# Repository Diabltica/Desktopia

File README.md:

# Desktopia

Desktopia is an open-source project for easy height control of your IKEA Skarsta/Trotten sit-stand desk, providing a
comfortable and customizable workspace experience.

A DC motor replaces the crank handle. Two boards control it: the **motherboard** under the desk top, and the **HMI board**
on the front edge with a round screen and five buttons. A time-of-flight sensor measures the desk height, so the desk can
go back to three saved heights at the press of a button.

## How it works

```mermaid
flowchart LR
    PSU[24 V power supply] -->|J1| MB
    subgraph MB[Motherboard - RP2040]
        direction TB
        SHUNT[2 mΩ shunt + INA226]
        SW[P-MOSFET supply switch]
        TOF[VL53L1CB height sensor]
    end
    MB -->|J5: switched 24 V| DRV[Cytron MD10C motor driver]
    MB -->|J6: DIR + PWM + GND| DRV
    DRV --> MOTOR[Motor] --> GEAR[Gearbox] --> DESK[Desk]
    MB <-->|RJ11 cord: 5 V + RS-485| HMI[HMI board - RP2040<br/>round screen + 5 buttons]
```

- The **motherboard** makes every decision. It reads the height (VL53L1CB), runs the state machine, drives the motor
  driver (direction + PWM, with ramps) and stores the presets in its flash. It also switches the driver's 24 V supply:
  on for a move, off after 5 minutes without one, and off at once if the motor current goes over the limit (INA226).
- The **HMI board** only displays what the motherboard sends and reports the button levels. It is powered by the
  motherboard through the RJ11 cord, which also carries the RS-485 link (250 kbaud, polled every 10 ms).
- If the cord, the sensor or the firmware fails, or the motor draws too much current, the motor stops: see the protections in
  [firmware/README.md](firmware/README.md#built-in-protections).

## Usage

| Action | Result |
|---|---|
| **Up / Down** held | the desk moves as long as the button is held |
| **Preset 1-3**, short press | the desk goes to the saved height |
| **Preset 1-3**, long press (2 s) | the current height is saved |
| any button during an automatic move | stop |

## Repository layout

| Folder | Content | Documentation |
|---|---|---|
| [hardware/desktopia/](hardware/desktopia/) | motherboard KiCad project (schematic, PCB) | [README](hardware/desktopia/README.md) |
| [hardware/desktopia_HMI/](hardware/desktopia_HMI/) | HMI board KiCad project (schematic, PCB) | [README](hardware/desktopia_HMI/README.md) |
| [hardware/kicad_library/](hardware/kicad_library/) | symbols and footprints shared by both KiCad projects (`JLCImport`, ...) | |
| [hardware/render.sh](hardware/render.sh) | renders the schematic / PCB / 3D images of the board READMEs; run by the [*Hardware images*](.github/workflows/hardware-images.yml) workflow on every push | |
| [firmware/desktopia/](firmware/desktopia/) | motherboard firmware (RP2040, PlatformIO) | [README](firmware/desktopia/README.md) |
| [firmware/desktopia_HMI/](firmware/desktopia_HMI/) | HMI board firmware (RP2040, PlatformIO) | [README](firmware/desktopia_HMI/README.md) |
| [firmware/shared/hmi_link/](firmware/shared/hmi_link/) | link protocol and screen model, compiled into both firmwares | [hmi_protocol.h](firmware/shared/hmi_link/hmi_protocol.h) |
| [firmware/sim/](firmware/sim/) | PC simulation of both boards from their real sources (Linux / WSL) | [README](firmware/README.md#simulation-bench-optional) |
| [mechanical/](mechanical/) | 3D-printed motor supports with silent blocks and jaw coupling (CadQuery scripts, STL / STEP, assembly report) | [README](mechanical/README.md) |
| [documentation/](documentation/) | VL53L1X datasheet | |

## Getting started

Tools: [KiCad 10](https://www.kicad.org/) for the boards, [PlatformIO](https://platformio.org/) for the firmwares.

1. **Boards**: open each KiCad project, update the PCB from the schematic and order it. Every assembled part has its
   JLCPCB / LCSC number in the `LCSC` field. Read the board READMEs first: both PCBs still have to be updated after
   the latest schematic changes.
2. **HMI firmware**: `cd firmware/desktopia_HMI && pio run -t upload` with the board in USB boot mode.
3. **Motherboard firmware**: `cd firmware/desktopia && pio run -t upload` (the board must be powered from its 24 V input).
4. **First power-up**: follow [the checklist](firmware/README.md#first-power-up-do-it-in-this-order), with the motor
   decoupled from the desk at first.

The firmware of both boards can be tested on a PC without any hardware (`firmware/sim/`, Linux / WSL).

## Status

- Firmwares: build with no warnings; tested in the PC simulation only.
- Schematics: ERC checked, netlists checked by script.
- PCBs: **not yet updated** to the latest schematics (RJ11 link, RP2040 HMI board, power input, current sensor, motor supply switch).
- Nothing has been tested on real boards yet.

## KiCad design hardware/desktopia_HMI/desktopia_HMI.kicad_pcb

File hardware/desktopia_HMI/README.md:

# Desktopia – HMI board

KiCad 10 project: `desktopia_HMI.kicad_sch`, `desktopia_HMI.kicad_pcb`. Firmware: [../../firmware/desktopia_HMI/](../../firmware/desktopia_HMI/README.md).

The HMI board sits on the front edge of the desk. It carries the round screen and the five buttons. Its own RP2040
draws the screen, debounces the buttons and answers the motherboard over RS-485. A single RJ11 cord brings both the
power and the link.

## Views

Interactive viewer (KiCanvas, opens the files of the `main` branch in the browser):
[schematic](https://kicanvas.org/?github=https://github.com/Diabltica/Desktopia/blob/main/hardware/desktopia_HMI/desktopia_HMI.kicad_sch) · [PCB](https://kicanvas.org/?github=https://github.com/Diabltica/Desktopia/blob/main/hardware/desktopia_HMI/desktopia_HMI.kicad_pcb).

The images below are rendered by [`../render.sh`](../render.sh) and committed by the
[*Hardware images*](../../.github/workflows/hardware-images.yml) workflow on every push that touches `hardware/`.
Click an image to open it full size.
The screen module model (`RoundLCD.wrl`) shows the real UI, taken from a screenshot of the simulator: it is generated by
[`round_lcd_3d.py`](../kicad_library/pcb/tools/round_lcd_3d.py) (rerun it after `firmware/sim/run.sh` to show another screen).
The picture is turned the way the firmware draws it for the module's position on the board (see J2 below).
The cord soldered to J3 (`Cable_6P6C_SolderPads.wrl`: about 1 cm of cord, the six wires, the solder joints and the
cable tie) is generated by [`cable_6p6c_3d.py`](../kicad_library/pcb/tools/cable_6p6c_3d.py).

Reading the schematic: every connection is a wire, with no labels. The parts sit next to the RP2040 pins they use:
the flash, crystal, USB, RUN and SWD on its left; the RS-485 transceiver, the buttons and the screen connector on its
right. Wires that cross without a dot are not connected: GPIO0 (to DI) over GPIO1 / GPIO2, and the screen CS (GPIO17)
over SCK / MOSI / DC, because the connector pin order differs from the GPIO order.
Each block has its own background and title colour (power and USB, RP2040 and flash, RS-485 link, buttons, screen).
Wires take the colour of their net class, as on the motherboard, with a legend at the bottom left of the sheet:
orange +5V, purple +3V3, pink +1V1, grey GND, teal the buses (USB, RS-485 and its UART, QSPI, screen SPI), green the
rest. See *PCB rules*.

**Schematic**

**PCB**

| Front | Back (mirrored) |
|---|---|
|  |  |

**3D**

| Top | Bottom |
|---|---|
|  |  |

## Blocks

| Block | Parts | Notes |
|---|---|---|
| MCU | U3 RP2040, Y1 12 MHz (C8 / C10 33 pF, R6 1k), decoupling C4-C7, C9, C11-C19 | standard Raspberry Pi minimal design |
| Flash | U2 W25Q128JVSIQ (16 MB QSPI) | the firmware uses 2 MB |
| 3.3 V | U1 XC6206P332 LDO, C1 / C2 (input), C3 (output) | supplies the RP2040, flash and transceiver |
| Link | J3 solder pads for the 6P6C cord, U4 SP3485EN (3.3 V RS-485), R8 120 Ω (not assembled) | UART0: GP0 TX, GP1 RX, GP2 DE + /RE |
| USB | J1 USB-C (G-Switch GT-USB-7010ASV), D1 SS14, R1 / R3 5.1k on CC, R4 / R2 22 Ω (D+ / D-) | bench flashing only |
| Boot / debug | SW1 BOOT (QSPI_SS through R5 1k), R7 10k RUN pull-up, TP1-TP4 SWD | no reset button: replug, or ground TP2 (RUN) |
| Screen | J2 7-pin connector, TP5-TP9 | GC9A01 240×240 round LCD on SPI0 |
| Buttons | SW2-SW6 Kailh Choc hot-swap sockets (PG1350) | to GND, internal pull-ups |

## Connectors

| Ref | Function | Pin-out |
|---|---|---|
| J1 | USB-C | flashing (UF2 bootloader) |
| J2 | round LCD | 1 = RST (GP21), 2 = CS (GP17), 3 = DC (GP20), 4 = MOSI (GP19), 5 = SCK (GP18), 6 = GND, 7 = +5 V |
| J3 | flat 6P6C cord to the motherboard, soldered (see below) | 1 = +5 V, 2 = GND, 3 = A, 4 = B, 5 = GND, 6 = +5 V |

J2 is numbered from the other end than the module's pin labels: the module's VCC, GND, SCL, SDA, DC, CS, RST are
J2 pins 7 down to 1.

The module sits with its pin header towards the buttons (J2 at 90°), turned 180° from the first layout: the firmware
turns the picture to match (`DISPLAY_ROTATION` 3 in `firmware/desktopia_HMI/include/hmi_config.h`).

Buttons: SW6 Up = GP11, SW5 Down = GP12, SW4 / SW3 / SW2 Preset 1 / 2 / 3 = GP13 / GP14 / GP15. On the PCB (front
view) they sit from SW2 on the left to SW6 on the right.

## The cord (J3)

The board sits at 45° under the front edge of the desk, in a wedge-shaped housing. An RJ11 jack would stand 12 mm
off the board, and its cord would leave parallel or perpendicular to the board, so at 45° to the desk either way.
The cord is therefore **soldered**: J3 (`Desktopia:Cable_6P6C_SolderPads`) has six 1 mm holes at 2.54 mm and two
slots for a 2.5 mm cable tie. The cord lies against the **bottom** of the board, leaves over the board edge (the
dashed *board edge* line on the Fab layer) and folds flat against the underside of the desk. Only the motherboard end
has an RJ11 plug, so the cord is unplugged there.

1. Take a flat 6-conductor cord (6P6C, sometimes sold as "RJ12") with a plug on one end, or crimp one.
   4-conductor cords (6P4C) do not work.
2. Strip about 10 mm of the jacket, strip and tin 3 mm of each wire.
3. Push the wires through the holes from the bottom and solder them on the top, **in their flat order**, edge wire
   on pad 1. Either direction is fine: the pin-out is symmetric, and
   a mirrored order only swaps A and B, which the firmware detects. Never cross two wires. The Fab layer shows the
   usual colours (white, black, red, green, yellow, blue), for reference only.
4. Put a cable tie through the two slots around the jacket, just behind the stripped end, its head under the cord.

## Power

- The motherboard supplies 5 V through the cord, limited by its 500 mA PTC. The screen module takes the 5 V and
  regulates its own 3.3 V. Its logic is driven at 3.3 V by the RP2040.
- On the bench, USB-C powers the board through the Schottky D1, which keeps the cord's 5 V out of the USB host.
  Unplug the cord at the motherboard while flashing over USB: otherwise the USB also feeds the motherboard's 5 V rail through the cord.

## Flashing

First flash: hold **SW1 (BOOT)**, plug the USB-C cable, then release SW1. The board appears as a USB drive (RPI-RP2).
Then run `pio run -t upload`, or copy `firmware.uf2` onto the drive. Later updates work the same way, or through SWD
on TP4 (SWCLK) / TP3 (SWDIO) / TP1 (GND).

## Test points

| TP | Net | TP | Net |
|---|---|---|---|
| TP1 | GND | TP6 | LCD_MOSI |
| TP2 | RUN (ground it to reset) | TP7 | LCD_DC |
| TP3 | SWDIO | TP8 | LCD_CS |
| TP4 | SWCLK | TP9 | LCD_RST |
| TP5 | LCD_SCK | | |

## Assembly (JLCPCB)

Order: 5 PCBs (2 layers, 139.7 × 33.27 mm, 1.6 mm, HASL with lead, green), **Economic PCBA of 2 boards, bottom side**
(every SMD part sits on the bottom). The pricing rules are the motherboard's (see *Assembly* in its
[README](../desktopia/README.md)): €2.82 per Extended SMD part number, none for Basic parts, no 0201, and the OSP finish
greys out Economic PCBA. Every assembled part has its LCSC number in the `LCSC` and `jlcpcb PartNumber` fields. The
production files come from the Fabrication Toolkit plugin (`production/`: Gerber zip, `bom.csv`, `positions.csv`).

- One Extended part number is left, U3 (RP2040, C2040), with no Basic or Preferred substitute. Everything else is
  Basic, and the MCU block uses the motherboard's part numbers.
- **J1** (USB-C, Extended) is excluded from the BOM and the position files: you solder it, as J3 on the motherboard
  (see the hand-soldering notes in its README). Its loading fee costs more than the part.
- Y1 is the Basic X322512MSB4SI (C9002). It is specified for a 20 pF load, hence the 33 pF capacitors C8 / C10.
- J1 is the G-Switch GT-USB-7010ASV (C2988369, $0.09). It replaces the HRO TYPE-C-31-M-12 ($0.19); the pins are the
  same, the footprint is KiCad's `USB_C_Receptacle_G-Switch_GT-USB-7010ASV`.
- U2 stays the W25Q128JVSIQ (16 MB) because it is a Basic part. The 2 MB and 4 MB Winbond parts are Extended at JLCPCB
  and cost $1.0 to $1.4. With the loading fee, they only pay off from about 4 boards per order.
- **SW2-SW6**, the Kailh Choc hot-swap sockets (CPG135001S30, C5333465), are out of stock at JLCPCB *and* LCSC
  (November 28, 2026, under every part number): they are excluded from the BOM and the position files (symbol and
  footprint), and you solder them by hand. Buy 10 (2 boards × 5) from a keyboard parts shop, with the Choc switches.
- Not assembled: R8 (termination, only for cords over ~5 m) and the test points. J2 takes the screen module's
  cable.

The JLCONE quotes (November 28, 2026, in euros, 2 boards, VAT and shipping excluded):

| # | JLCPCB does not assemble | PCB (engineering + board) | Setup + stencil | Components | Extended fee | SMT | N₂ | JLCPCB |
|---|---|---|---|---|---|---|---|---|
| 1 | SW2-SW6 | 5.76 (3.65 + 2.10) | 8.95 | 7.34 | 5.65 (2) | 0.52 | 0.79 | **28.99** |
| 2 | 1 + J1 (**chosen**) | 5.76 | 8.95 | 7.03 | 2.82 (1) | 0.42 | 0.79 | **25.76** |

- The board is longer than 100 mm, so it misses the PCB special offer of the motherboard (€1.83 for 5) and pays the
  €3.65 engineering fee. It needs no X-ray inspection (the motherboard's €3.01 comes with its other leadless parts).
- Option 2 saves €2.84 once J1 is bought at LCSC (5 for both boards' USB-C: $0.42). Quote 2 was checked with the
  files of `production/`.
- Order both boards together: one parcel, one shipping fee. Each board stays its own PCBA order, so the RP2040 loading
  fee, the setup and the stencil are paid once per board. The LCSC parts of both boards are in the common cart
  [`../lcsc_cart.csv`](../lcsc_cart.csv) (upload it at LCSC's *BOM Tool*).
- 3D model of J1: the LCSC one (`kicad_library/pcb/JLCImport.3dshapes`), as on the motherboard. R8 has its model but
  is marked DNP, so the 3D view hides it.

## PCB rules

The method and the sources are the motherboard's (see *PCB rules* in its [README](../desktopia/README.md)): 2 layers,
FR-4 1.6 mm, 1 oz (35 µm) copper, made by JLCPCB, track currents from IPC-2221 at ΔT 10 °C. Every net here is at 5 V
or less, so one clearance fits all: 0.2 mm (IPC-2221B, uncoated pads up to 15 V: 0.13 mm; JLCPCB: 0.10 mm).

- *Board Setup → Constraints*: JLCPCB's absolute minimums, the same as on the motherboard (0.10 mm track and gap; via
  0.45 mm with a 0.2 mm hole; 0.2 mm hole to hole and hole to copper; 0.3 mm to the board edge; 0.1 mm solder mask web;
  1 mm / 0.15 mm silkscreen text).
- *Board Setup → Net Classes*: routing width, clearance and via of each class (below), also in the toolbar lists.
- [`desktopia_HMI.kicad_dru`](desktopia_HMI.kicad_dru) (*Board Setup → Custom Rules*): the DRC minimum width of each
  class, JLCPCB's hole and silkscreen rules, and the exceptions.

| Class | Nets | Track: routing / DRC min | Clearance | Via: pad / hole | A track carries |
|---|---|---|---|---|---|
| `Default` | crystal, SWD, RUN, buttons, BOOT, CC | 0.2 / 0.15 mm | 0.2 mm | 0.6 / 0.3 mm | 0.7 A |
| `Buses` | USB D+ / D-, RS-485 A / B and its UART, QSPI, screen SPI | 0.2 / 0.15 mm, pairs 0.2 mm with a 0.2 mm gap | 0.2 mm | 0.6 / 0.3 mm | 0.7 A |
| `Power_1V1` | +1V1 (RP2040 core) | 0.3 / 0.2 mm | 0.2 mm | 0.6 / 0.3 mm | 1.0 A |
| `Power_3V3` | +3V3 (XC6206, 0.2 A at most) | 0.3 / 0.2 mm | 0.2 mm | 0.6 / 0.3 mm | 1.0 A |
| `GND` | GND (pour on both layers) | 0.4 / 0.2 mm | 0.2 mm | 0.6 / 0.3 mm | 1.2 A |
| `Power_5V` | +5V, USB VBUS (0.5 A at most: the motherboard's PTC) | 0.4 / 0.2 mm | 0.2 mm | 0.6 / 0.3 mm | 1.2 A |

- A 0.6 / 0.3 mm via carries 0.7 A (ΔT 10 °C, 18 µm of hole plating): one is enough for every rail of this board.
- The RP2040 sets the 0.2 mm width: its 0.4 mm pitch pads are 0.2 mm wide and 0.2 mm apart, so a 0.2 mm track enters a
  pad 0.2 mm from the next one. The power tracks neck down to 0.2 mm (their DRC minimum) at its pins.
- Exceptions:
  - Pads of one footprint keep the maker's land pattern, at 0.15 mm at least: the USB-C GND pads sit 0.19 mm from the
    connector's locating holes.
  - Tracks inside the courtyard of U3 or J1 may pass 0.15 mm from other copper.
  - Holes of one footprint keep the 0.2 mm via spacing: the via ring of the M2 mounting holes is 0.35 mm apart.
- The other JLCPCB rules are the motherboard's: vias at least 0.6 / 0.3 mm, holes 0.2 to 6.3 mm, NPTH 0.5 mm at least,
  PTH annular ring 0.18 mm, pad holes of two footprints 0.45 mm apart, PTH hole to track 0.35 mm, silkscreen 0.15 mm
  from pads.

## PCB: what to do before ordering

The PCB is routed (no unconnected item), and the routing passes the net class rules. The DRC of November 11, 2026
still finds:

- **TP1-TP9 are missing from the PCB.** They are in the schematic, but it changed after the last PCB update. So the
  board has no SWD (TP1 / TP3 / TP4, see *Flashing*), RUN or screen test points. Run *Update PCB from Schematic*,
  then place and route them.
- **7 thermal reliefs with one spoke instead of two** (errors), all on B.Cu: pad 2 of C5, C16 and C18, and the four
  GND pads of J1. Add a track or a via to the pour, or give these pads a solid connection.
- **5 GND vias stacked at (84.2, 83.8) mm**: keep one.
- **The silkscreen labels of J3** (+5V, GND, A, B) are 0.6 mm high, under JLCPCB's 1 mm / 0.15 mm, and may not print.
  They come from the footprint ([`cable_6p6c_fp.py`](../kicad_library/pcb/tools/cable_6p6c_fp.py)).
- Warnings only:
  - silkscreen closer than 0.15 mm to pads (171): JLCPCB trims silkscreen off pads;
  - silkscreen over copper (65);
  - the H1 / H2 references and the J2 outline clipped by the board edge (4);
  - the NPTH holes of the PG1350 sockets drawn twice in their footprint (5).

For the layout:

- Place J3 against the edge that faces the desk, with its dashed *board edge* line on the outline, so the cord leaves
  straight over the edge. Keep the area between the pads and the edge free of parts (cable tie, wires).
- Place the RP2040 decoupling capacitors next to each supply pin, keep a solid ground under the QFN, and keep the
  crystal and the QSPI flash close to the RP2040.

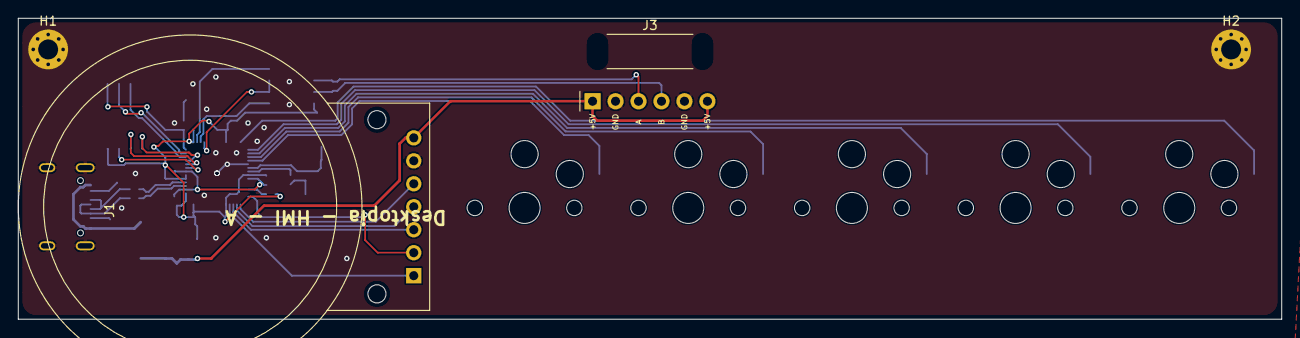
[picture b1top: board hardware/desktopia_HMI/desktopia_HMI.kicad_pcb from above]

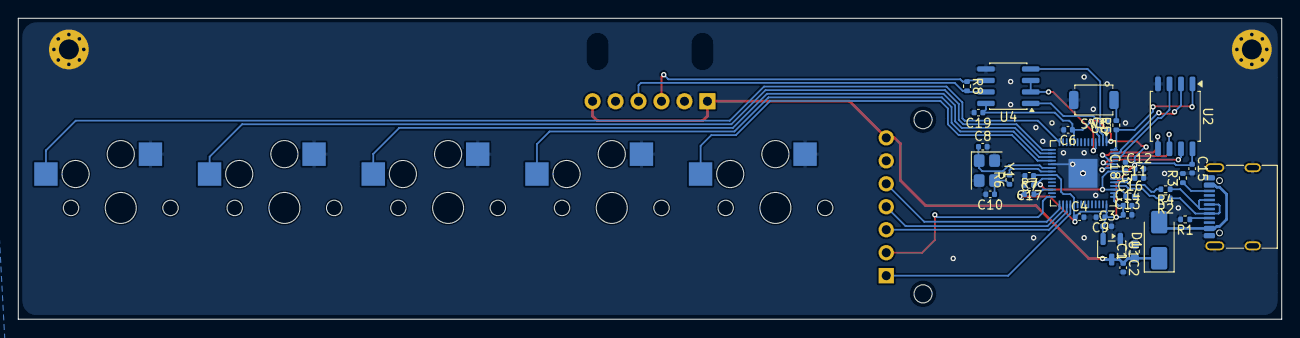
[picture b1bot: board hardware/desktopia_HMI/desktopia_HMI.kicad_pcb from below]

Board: 2 copper layers, 139.7 x 33.3 mm, 44 parts (35 on the bottom side), 37 nets.

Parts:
C1: 10uF; C_0603_1608Metric
C2, C3, C14, C16: 1uF; C_0402_1005Metric
C4, C5, C6, C7, C9, C11, C12, C13, C15, C17, C18, C19: 100nF; C_0402_1005Metric
C8, C10: 33pF; C_0402_1005Metric
D1: SS14; D_SMA
H1, H2: MountingHole_Pad; MountingHole_2.2mm_M2_Pad_Via
J1: GT-USB-7010ASV; USB_C_Receptacle_G-Switch_GT-USB-7010ASV
J2: LCD_Connector; LCD_round_screen
J3: 6P6C cord, soldered; Cable_6P6C_SolderPads
R1, R3: 5.1k; R_0402_1005Metric
R2, R4: 22; R_0402_1005Metric
R5, R6: 1k; R_0402_1005Metric
R7: 10k; R_0402_1005Metric
R8: 120; R_0402_1005Metric
SW1: TS-1088-AR02016; SW_SPST_TS-1088-xR020
SW2, SW3, SW4, SW5, SW6: SW_Push; PG1350
U1: XC6206P332MR; SOT-23-3
U2: W25Q128JVSIQ; SOIC-8_5.3x5.3mm_P1.27mm
U3: RP2040; QFN-56-1EP_7x7mm_P0.4mm_EP3.2x3.2mm
U4: SP3485EN-L/TR; SOIC-8_3.9x4.9mm_P1.27mm
Y1: 12MHz; Crystal_SMD_3225-4Pin_3.2x2.5mm

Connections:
+1V1: C16.1, C17.1, C18.1, U3.23 (DVDD), U3.45 (VREG_VOUT), U3.50 (DVDD)
+3V3: C3.1, C4.1, C5.1, C6.1, C7.1, C9.1, C11.1, C12.1, C13.1, C14.1, C15.1, C19.1, R7.1, U1.2 (VO), U2.8 (VCC), U3.1 (IOVDD), U3.10 (IOVDD), U3.22 (IOVDD), U3.33 (IOVDD), U3.42 (IOVDD), U3.43 (ADC_AVDD), U3.44 (VREG_VIN), U3.48 (USB_VDD), U3.49 (IOVDD), U4.8 (VCC)
+5V: C1.1, C2.1, D1.1 (K), J2.7, J3.1, J3.6, U1.3 (VI)
/D+: R4.2, U3.47 (USB_DP)
/D-: R2.2, U3.46 (USB_DM)
/data+: J3.4, R8.2, U4.7 (B)
/data-: J3.3, R8.1, U4.6 (A)
GND: C1.2, C2.2, C3.2, C4.2, C5.2, C6.2, C7.2, C8.2, C9.2, C10.2, C11.2, C12.2, C13.2, C14.2, C15.2, C16.2, C17.2, C18.2, C19.2, H1.1 (1_1), H2.1 (1_1), J1.A1 (GND), J1.A12 (GND), J1.B1 (GND), J1.B12 (GND), J1.SH (SHIELD), J2.6, J3.2, J3.5, R1.2, R3.2, SW1.2, SW2.1, SW3.1, SW4.1, SW5.1, SW6.1, U1.1 (GND), U2.4 (GND), U3.19 (TESTEN), U3.57 (GND), U4.5 (GND), Y1.2 (G), Y1.4 (G)
unnamed: C10.1, R6.1, Y1.3
unnamed: D1.2 (A), J1.A4 (VBUS), J1.A9 (VBUS), J1.B4 (VBUS), J1.B9 (VBUS)
unnamed: J1.A5 (CC1), R1.1
unnamed: J1.B5 (CC2), R3.1
unnamed: J1.A6 (D+), J1.B6 (D+), R4.1
unnamed: J1.A7 (D-), J1.B7 (D-), R2.1
unnamed: J2.1, U3.32 (GPIO21)
unnamed: J2.2, U3.28 (GPIO17)
unnamed: J2.3, U3.31 (GPIO20)
unnamed: J2.4, U3.30 (GPIO19)
unnamed: J2.5, U3.29 (GPIO18)
unnamed: R5.2, SW1.1
unnamed: U2.6 (CLK), U3.52 (QSPI_SCLK)
unnamed: U2.5 (DI/IO_{0}), U3.53 (QSPI_SD0)
unnamed: U2.2 (DO/IO_{1}), U3.55 (QSPI_SD1)
unnamed: R5.1, U2.1 (~CS), U3.56 (~QSPI_SS)
unnamed: U2.7 (~HOLD/~RESET/IO_{3}), U3.51 (QSPI_SD3)
unnamed: U2.3 (~WP/IO_{2}), U3.54 (QSPI_SD2)
unnamed: U3.2 (GPIO0), U4.4 (DI)
unnamed: U3.3 (GPIO1), U4.1 (RO)
unnamed: U3.4 (GPIO2), U4.2 (~RE), U4.3 (DE)
unnamed: SW6.2, U3.14 (GPIO11)
unnamed: SW5.2, U3.15 (GPIO12)
unnamed: SW4.2, U3.16 (GPIO13)
unnamed: SW3.2, U3.17 (GPIO14)
unnamed: SW2.2, U3.18 (GPIO15)
unnamed: R7.2, U3.26 (RUN)
unnamed: C8.1, U3.20 (XIN), Y1.1
unnamed: R6.2, U3.21 (XOUT)

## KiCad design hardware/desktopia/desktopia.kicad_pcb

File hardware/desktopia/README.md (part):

# Desktopia – motherboard

KiCad 10 project: `desktopia.kicad_sch`, `desktopia.kicad_pcb`. Firmware: [../../firmware/desktopia/](../../firmware/desktopia/README.md).

The motherboard sits under the desk top. It takes the 24 V supply and passes it through a current shunt and a MOSFET
switch to its own H-bridge (DRV8701E gate driver, four N-MOSFETs), which drives the motor. The bridge can be bypassed:
J5 / J6 still give the switched 24 V and DIR / PWM to an external driver. The board measures the height, powers the HMI
board and talks to it.

## Views

Interactive viewer (KiCanvas, opens the files of the `main` branch in the browser):
[schematic](https://kicanvas.org/?github=https://github.com/Diabltica/Desktopia/blob/main/hardware/desktopia/desktopia.kicad_sch) · [PCB](https://kicanvas.org/?github=https://github.com/Diabltica/Desktopia/blob/main/hardware/desktopia/desktopia.kicad_pcb).

The images below are rendered by [`../render.sh`](../render.sh) and committed by the
[*Hardware images*](../../.github/workflows/hardware-images.yml) workflow on every push that touches `hardware/`.
Click an image to open it full size.
The 3D view shows the JP6 wire link fitted, and the plugs of J1 / J5 / J6 / J7 in their headers: the
`Desktopia:PluggableHeader_*` footprints carry KiCad's Phoenix Contact header model and a plug generated by
[`pluggable_plug_3d.py`](../kicad_library/pcb/tools/pluggable_plug_3d.py) (the footprints by
[`pluggable_header_fp.py`](../kicad_library/pcb/tools/pluggable_header_fp.py)).

Reading the schematic: connections are drawn as wires. A label only appears where a net leaves one block for another,
at the MCU pin and at the block it reaches (`TOF_SCL`, `TOF_SDA`, `TOF_INT`, `INA_SCL`, `INA_SDA`, `I_ALERT`,
`Mpwm`, `Mdir`, `nSLEEP`, `nFAULT`, `MOTOR_PWR`, `RX` / `TX` / `DE` for RS-485, `+5V_HMI`, `MOTOR_SW`). `D_+` / `D_-` only name the USB pair, `MOTOR_24V` a 15 A net. In the H-bridge
block, `OUT1` / `OUT2` join the two legs to J7, `LS_SRC` joins the low-side sources to the shunts R27 / R28 under U7,
and `VM` names the bridge supply after JP6. The RP2040 decoupling capacitors sit in two rows at the top of the MCU
block, each on the supply it decouples (`+3V3` / `+1V1`); the note under the RP2040 says which pin each one belongs to.
Wires that cross without a dot are not connected: D+ over D- before the RP2040, Vin+ over Vin- at the INA226.

Colours: each block has its own background and title colour (24 V input and 5 V supply, MCU, height sensor, HMI link,
motor supply, H-bridge). Wires and labels take the colour of their net class, with a legend on the sheet, left of the
MCU:

| Colour | Net class | Nets |
|---|---|---|
| red, thick | `Power_24V` | `+24V`, `MOTOR_24V`, `MOTOR_SW`, `VM`, `OUT1` / `OUT2`, `LS_SRC`: the 15 A path |
| orange | `Power_5V` | `+5V`, `+5V_HMI`, USB-C VBUS before D5 |
| purple | `Power_3V3` | `+3V3` (U9: RP2040, flash, RS-485 transceiver, INA226) |
| olive | `Power_2V8` | `+2V8` (height sensor and its side of Q1 / Q2 / Q3) |
| pink | `Power_1V1` | `+1V1` (RP2040 core, from its internal regulator) |
| grey | `GND` | `GND` |
| blue | `Motor_command` | `Mdir`, `Mpwm`, `nSLEEP`, `nFAULT`, `MOTOR_PWR`, `I_ALERT`, and PH / EN / nSLEEP / nFAULT after JP2-JP5 |
| magenta | `Gate_drive` | the four gates of the H-bridge |
| brown | `Current_sense` | Kelvin lines: Vin+ / Vin- of the INA226, SP / SN of the DRV8701 |
| teal | `Buses` | both I2C buses (ToF: both sides of Q1 / Q2; INA226), ToF interrupt, RS-485, USB D+ / D-, QSPI flash |
| green | `Default` | everything else |
| green (PCB only) | `HV_signal`, `Switch_node` | 24-38 V low-current nets (charge pump, bootstrap, Q5 gate), TPS5430 switch node |

The classes and their net patterns are in the project settings (*Schematic Setup → Net Classes*). Unnamed nets are
matched by their KiCad name (`Net-(Q6-G)`...): after renaming one of these parts, update its pattern. Each class also
sets the PCB track width, clearance and via: see *PCB rules*.

**Schematic**

**PCB**

| Front | Back (mirrored) |
|---|---|
|  |  |

**3D**

| Top | Bottom |
|---|---|
|  |  |

## Blocks

| Block | Parts | Notes |
|---|---|---|
| 24 V input | J1 (5.08 mm pluggable terminal, 15 A), D2 SMBJ28A (600 W TVS), C6 (100 µF 50 V bulk), C5 (10 µF 50 V ceramic), TP5 | J1 carries the full motor current. D2 clamps motor and hot-plug spikes below the 40 V absolute maximum of U2 and U6 |
| 24 V → 5 V | U2 TPS5430 (3 A buck), L1 22 µH (1.8 A, shielded), D1 SS34 (3 A), C3 10 nF (boot), C7 + C8 (2 × 47 µF ceramic), R4 / R7 (10k / 3.3k → 4.92 V), C4 / R9 / C12 / C11 (compensation) | 1.5 A available. ENA left open, see *Known issues* |
| Motor current | R23 2 mΩ 3 W shunt, U6 INA226 (I2C 0x40 on its own bus, supplied at 3.3 V), C22, R25, C23, R33 / R34 (I2C pull-ups) | ±41 A full scale; alert on GP27 (R25 4.7k pull-up to +3V3, C23 100 pF against motor spikes). The firmware cuts the PWM and Q5 on an alert |
| Motor supply switch | Q5 IPD90P04P4-05 (P-MOSFET, −40 V, 4.7 mΩ, TO-252), Q4 BSS138 (gate driver), R21 / R20 100k (gate divider), R22 10k (pull-down), D3 BZT52C15 (V<sub>GS</sub> clamp), C21 100 nF 50 V (soft start), D4 SS34, TP13 | no relay. `MOTOR_PWR` (GP12) high → Q4 on → V<sub>GS</sub> −12 V → J5 powered. R22 keeps it off while the MCU is in reset or blank. See *Power* |
| MCU | U4 RP2040 (QFN-56), U8 W25Q128JVSIQ (16 MB QSPI flash), Y1 12 MHz (C15 / C16 33 pF, R32 1k), decoupling C13 / C14 / C17 / C19 / C33-C41 (0402), BOOT1 + R31 (BOOTSEL), RST1 + R12 (RUN), TP4 / TP7 (SWD), TP11 (RUN) | the standard Raspberry Pi minimal design, as on the HMI board. USB bootloader in ROM: BOOT1 held at reset → USB drive. 3.3 V I/O, none of them 5 V tolerant |
| 3.3 V | U9 XC6206P332MR (from +5V), C42 / C43, TP10 | RP2040, flash, RS-485 transceiver, INA226: about 50 mA |
| USB | J3 USB-C (G-Switch GT-USB-7010ASV), R13 / R15 22 Ω, R18 / R19 5.1k on CC, D5 SS34 | flashing, debug logs and bench power: VBUS feeds +5V through D5 (logic, sensor and HMI board, not the motor). See *Power* |
| Height sensor | U3 VL53L1CB, U1 XC6206P282 (2.8 V LDO), Q1 / Q2 / Q3 BSS138 (3.3 V ↔ 2.8 V level shifters: SCL, SDA, GPIO1), R1 / R5 / R10 (3.3 V side), R2 / R6 / R11 (2.8 V side), R8, TP15-TP17 | XSHUT tied high (R8). GPIO1 (data ready) reaches GP11 as `TOF_INT` through Q3. See *I2C bus* |
| Motor command | J5 (switched 24 V out, `MOTOR_SW`), J6 (DIR, PWM, GND), R26 / R24 (10k pull-downs on PWM / DIR) | DIR / PWM go to the on-board H-bridge, and to J6 for an external driver (Cytron MD10C R3) when the bridge is bypassed. The pull-downs keep the motor stopped while the MCU is in reset, in the bootloader or blank |
| H-bridge | U7 DRV8701E (gate driver, PH/EN), Q6 / Q7 / Q8 / Q9 BSC028N06NS (60 V, 2.8 mΩ, SuperSO8), C24 / C25 (2 × 470 µF 50 V low impedance), C26 / C27 (10 µF 50 V), C28 (100 nF, VM), C29 (VCP), C30 (charge pump), C31 / C32 (AVDD / DVDD), R27 / R28 (2 × 2 mΩ 3 W shunt, Kelvin), R29 / R30 (VREF divider), TP14 (SO), J7 (motor), JP2-JP5 (solder jumpers), JP6 (wire link) | PH = `Mdir`, EN = `Mpwm` (up to 100 kHz, 25 kHz planned). EN low = brake. `nSLEEP` (GP18) low = bridge off, `nFAULT` (GP19) = fault. Current limited cycle by cycle at about 14.6 A. See *H-bridge* |
| HMI link | J4 RJ11 6P6C, U5 SP3485EN (3.3 V RS-485, as on the HMI board), F1 500 mA PTC, R14 / R17 4.7k bias (to +3V3 / GND), R16 120 Ω (not assembled), C18 / C20 | UART1: GP4 TX → DI, GP9 RX ← RO, GP8 DE + /RE (labels `TX` / `RX` / `DE`). See the link section of the firmware README |
| Power LED | LED1, R3 (470 Ω, 6 mA), JP1 solder jumper | LED off until JP1 is bridged |

## Connectors

| Ref | Function | Pin-out |
|---|---|---|
| J1 | 24 V supply input | 1 = +24 V, 2 = GND |
| J3 | USB-C: flashing, debug logs, bench power for the logic | USB 2.0 full speed |
| J4 | RJ11 cord to the HMI board | 1 = +5 V, 2 = GND, 3 = A, 4 = B, 5 = GND, 6 = +5 V |
| J5 | supply out to an external motor driver (after the shunt and Q5) | 1 = MOTOR_SW, 2 = GND |
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
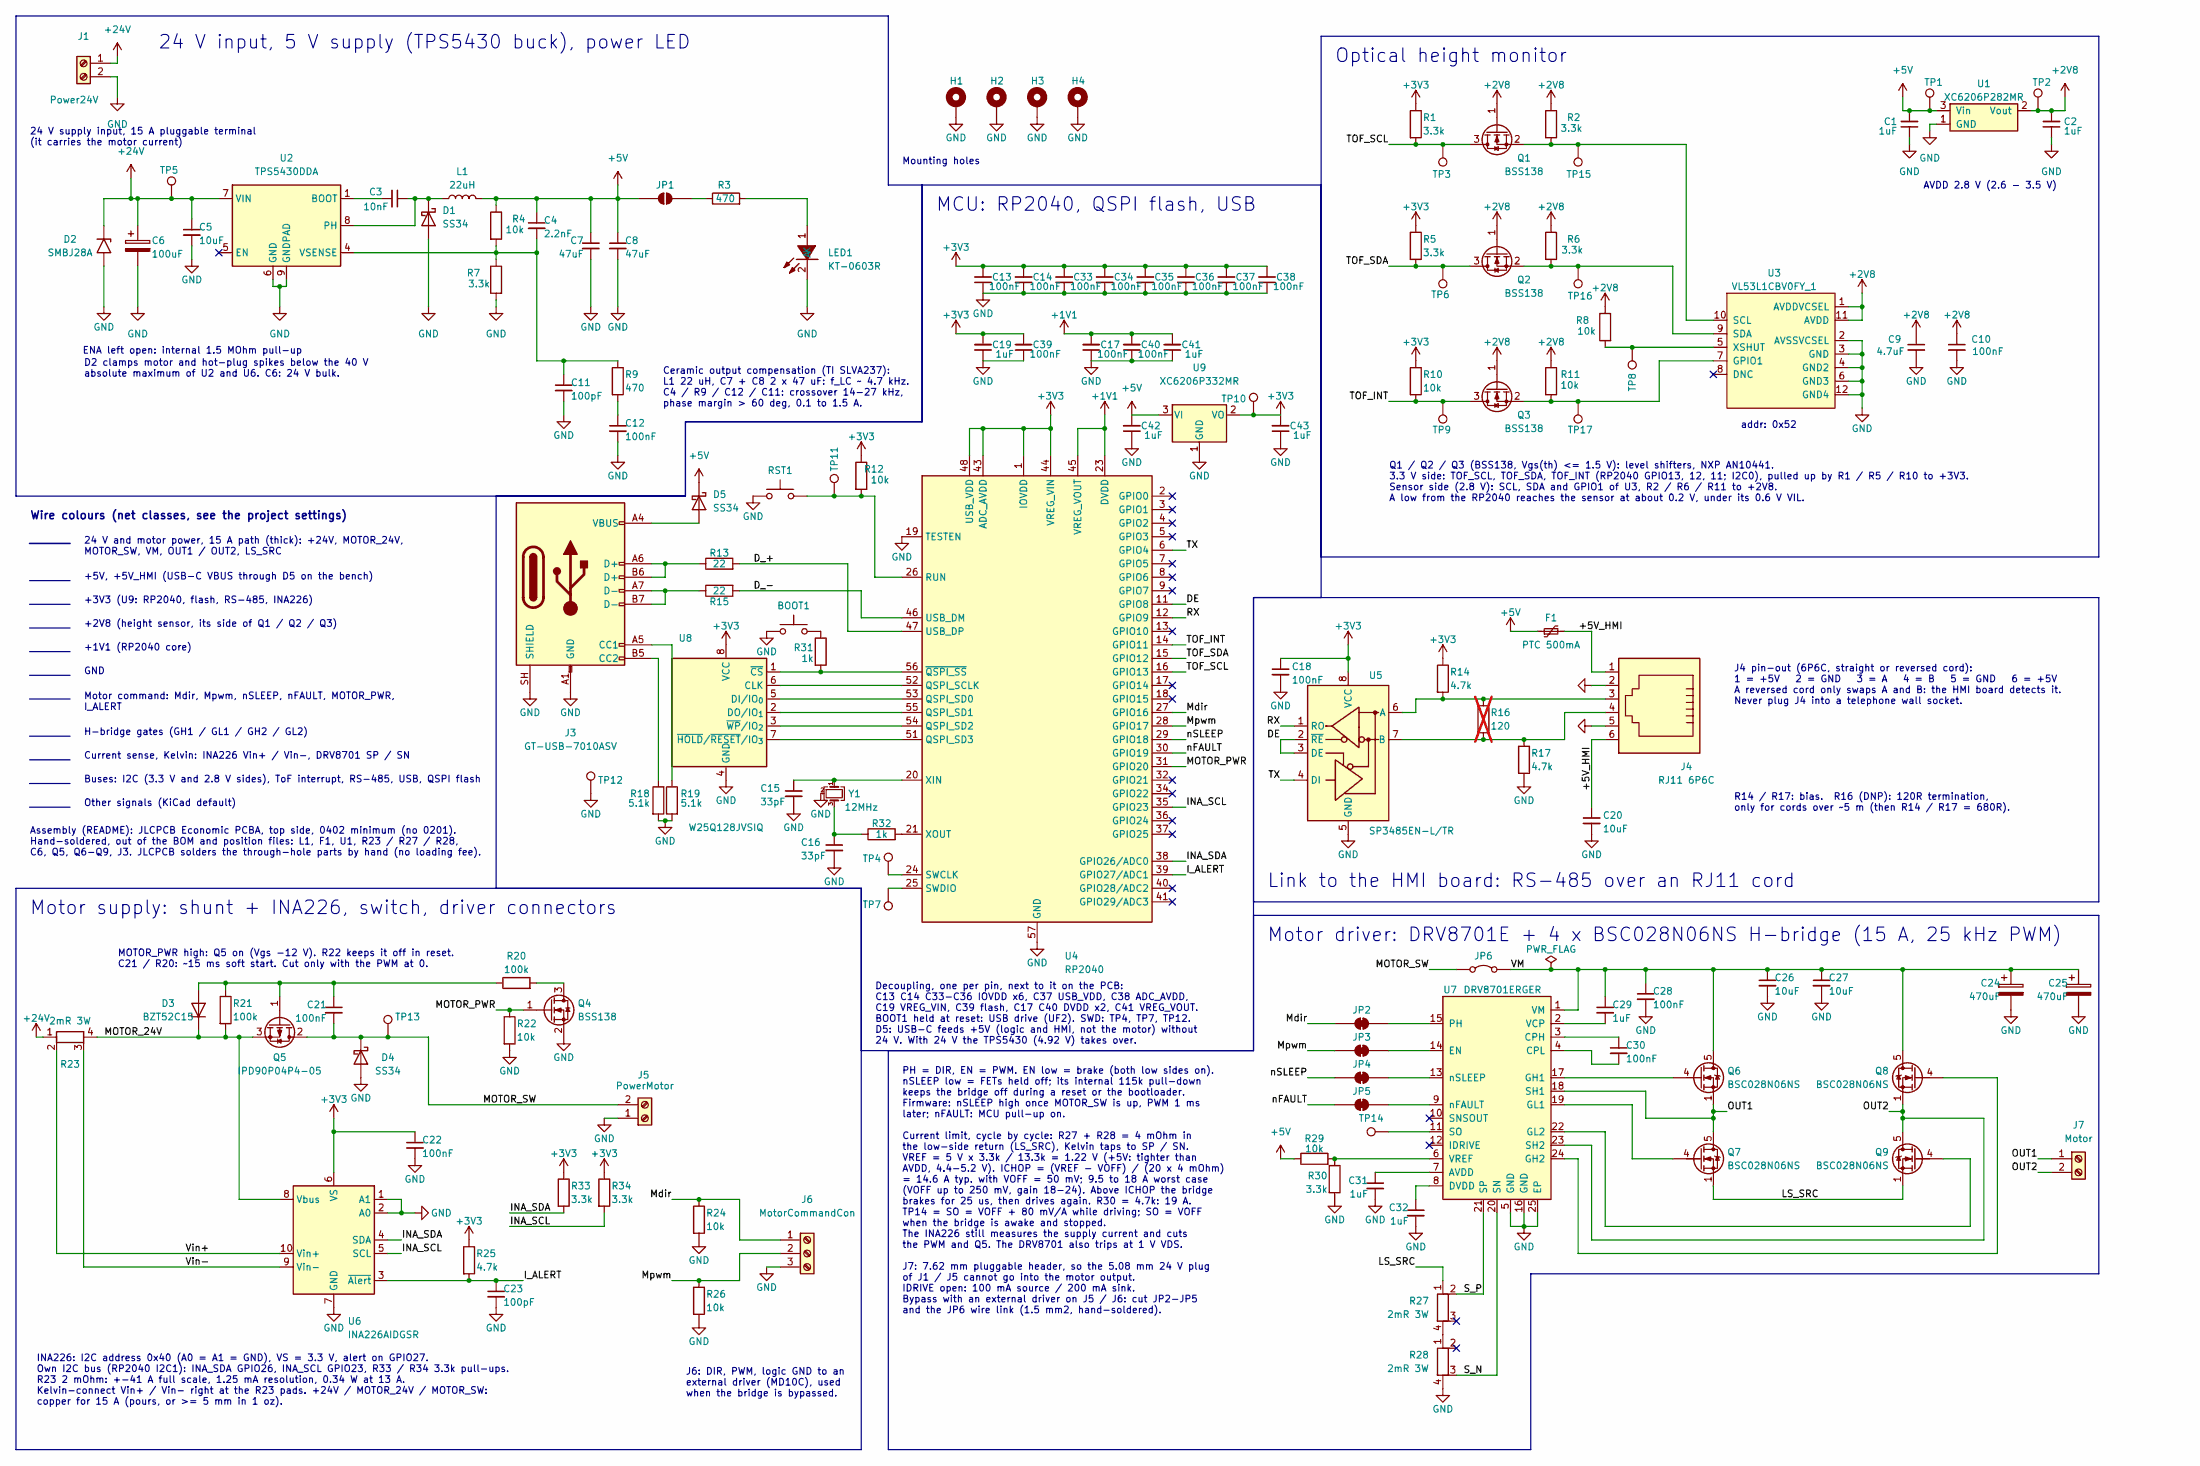
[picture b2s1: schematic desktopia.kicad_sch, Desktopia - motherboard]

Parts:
BOOT1: TS-1088-AR02016; SW_SPST_TS-1088-xR020; LCSC C720477
C1, C2, C19, C29, C31, C32, C41, C42, C43: 1uF; C_0402_1005Metric; jlcpcb PartNumber C52923
C3: 10nF; C_0402_1005Metric; jlcpcb PartNumber C15195
C4: 2.2nF; C_0603_1608Metric; Manufacturer Part 0603B222K500NT; LCSC C1604
C5, C26, C27: 10uF; C_1206_3216Metric; Voltage 50V X5R; LCSC C13585
C6: 100uF; CP_Elec_8x10; Voltage 50V; Manufacturer Part RVT1H101M0810; LCSC C970687
C7, C8: 47uF; C_1206_3216Metric; Voltage 10V X5R; Manufacturer Part CL31A476MPHNNNE; LCSC C96123
C9: 4.7uF; C_0402_1005Metric; jlcpcb PartNumber C23733
C10, C13, C14, C17, C18, C33, C34, C35, C36, C37, C38, C39, C40: 100nF; C_0402_1005Metric; jlcpcb PartNumber C1525
C11, C23: 100pF; C_0402_1005Metric; Manufacturer Part 0402CG101J500NT; LCSC C1546
C12: 100nF; C_0402_1005Metric; Manufacturer Part CL05B104KO5NNNC; LCSC C1525
C15, C16: 33pF; C_0402_1005Metric; jlcpcb PartNumber C1562
C20: 10uF; C_0603_1608Metric; jlcpcb PartNumber C19702
C21, C28, C30: 100nF; C_0402_1005Metric; Voltage 50V X7R; Manufacturer Part CL05B104KB54PNC; LCSC C307331
C22: 100nF; C_0402_1005Metric; LCSC C1525
C24, C25: 470uF; CP_Radial_D10.0mm_P5.00mm; Voltage 50V; Manufacturer Part 50ZLJ470M10X20; LCSC C2902875
D1, D5: SS34; D_SMA; jlcpcb PartNumber C8678
D2: SMBJ28A; D_SMB; Manufacturer Part SMBJ28A; LCSC C19077582
D3: BZT52C15; D_SOD-123; Manufacturer Part BZT52C15; LCSC C19077412
D4: SS34; D_SMA; Manufacturer Part SS34; LCSC C8678
F1: PTC 500mA; Fuse_1206_3216Metric; LCSC C720075
H1, H2, H3, H4: MountingHole_Pad; MountingHole_3.2mm_M3_Pad_Via
J1: Power24V; PluggableHeader_2EDGRC_1x02_P5.08mm_Horizontal; Manufacturer Part KF2EDGRC-5.08-2P; LCSC C441236
J3: GT-USB-7010ASV; USB_C_Receptacle_G-Switch_GT-USB-7010ASV; Manufacturer Part GT-USB-7010ASV; LCSC C2988369
J4: RJ11 6P6C; RJ12_Amphenol_54601-x06_Horizontal; LCSC C3097716
J5: PowerMotor; PluggableHeader_2EDGRC_1x02_P5.08mm_Horizontal; Manufacturer Part KF2EDGRC-5.08-2P; LCSC C441236
J6: MotorCommandCon; PluggableHeader_15EDGRC_1x03_P3.81mm_Horizontal; Manufacturer Part WJ15EDGRC-3.81-03P-14-00A; LCSC C8406
J7: Motor; PluggableHeader_2EDGRC_1x02_P7.62mm_Horizontal; Manufacturer Part KF2EDGRC-7.62-2P; LCSC C441246
JP1: SolderJumper_2_Open; SolderJumper-2_P1.3mm_Open_TrianglePad1.0x1.5mm
JP2, JP3, JP4, JP5: SolderJumper_2_Bridged; SolderJumper-2_P1.3mm_Bridged_RoundedPad1.0x1.5mm
JP6: 1.5 mm2 wire; SolderWire-1.5sqmm_1x02_P6mm_D1.7mm_OD3mm
L1: 22uH; L_Sunlord_SWPA6045S; Manufacturer Part CKCS6045-22uH/M; jlcpcb PartNumber C354634
LED1: KT-0603R; Manufacturer Part KT-0603R; LCSC C2286
Q1, Q2, Q3, Q4: BSS138; SOT-23; Manufacturer Part BSS138; LCSC C7420339
Q5: IPD90P04P4-05; TO-252-2; Manufacturer Part IPD90P04P405; LCSC C536914
Q6, Q7, Q8, Q9: BSC028N06NS; TDSON-8-1; Manufacturer Part BSC028N06NSATMA1; LCSC C148250
R1, R2, R5, R6, R7, R30, R33, R34: 3.3k; R_0402_1005Metric; jlcpcb PartNumber C25890
R3: 470; R_0402_1005Metric; jlcpcb PartNumber C25117
R4, R8, R11, R12: 10k; R_0402_1005Metric; jlcpcb PartNumber C25744
R9: 470; R_0402_1005Metric; Manufacturer Part 0402WGF4700TCE; LCSC C25117
R10, R22, R24, R26, R29: 10k; R_0402_1005Metric; Manufacturer Part 0402WGF1002TCE; LCSC C25744
R13, R15: 22; R_0402_1005Metric; jlcpcb PartNumber C25092
R14, R17: 4.7k; R_0402_1005Metric; jlcpcb PartNumber C25900
R16: 120; R_0402_1005Metric; jlcpcb PartNumber C25079; not fitted
R18, R19: 5.1k; R_0402_1005Metric; jlcpcb PartNumber C25905
R20, R21: 100k; R_0402_1005Metric; Manufacturer Part 0402WGF1003TCE; LCSC C25741
R23, R27, R28: 2mR 3W; R_2512_CurrentSensing_opti; LCSC C154685
R25: 4.7k; R_0402_1005Metric; LCSC C25900
R31, R32: 1k; R_0402_1005Metric; jlcpcb PartNumber C11702
RST1: TS-1088-AR02016; SW_SPST_TS-1088-xR020; LCSC C720477
TP1, TP2, TP3, TP4, TP5, TP6, TP7, TP8, TP9, TP10, TP11, TP12, TP13, TP14, TP15, TP16, TP17: TestPoint; TestPoint_Pad_D1.0mm
U1: XC6206P282MR; SOT-23-3; Manufacturer Part XC6206P282MR; LCSC C347374
U2: TPS5430DDA; TI_SO-PowerPAD-8_ThermalVias; jlcpcb PartNumber C9864
U3: VL53L1CBV0FY_1; Manufacturer Part VL53L1CBV0FY/1; LCSC C2970716
U4: RP2040; QFN-56-1EP_7x7mm_P0.4mm_EP3.2x3.2mm; LCSC C2040
U5: SP3485EN-L/TR; SOIC-8_3.9x4.9mm_P1.27mm; LCSC C8963
U6: INA226AIDGSR; TSSOP-10_3x3mm_P0.5mm; LCSC C49851
U7: DRV8701ERGER; Texas_RGE0024H_VQFN-24-1EP_4x4mm_P0.5mm_EP2.7x2.7mm_Thermal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; Manufacturer Part DRV8701ERGER; LCSC C90964
U8: W25Q128JVSIQ; SOIC-8_5.3x5.3mm_P1.27mm; LCSC C97521
U9: XC6206P332MR; SOT-23-3; LCSC C5446
Y1: 12MHz; Crystal_SMD_3225-4Pin_3.2x2.5mm; LCSC C9002

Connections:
+1V1: C17.2, C40.2, C41.2, U4.23 (DVDD), U4.45 (VREG_VOUT), U4.50 (DVDD)
+2V8: C2.2, C9.1, C10.1, Q1.1 (G), Q2.1 (G), Q3.1 (G), R2.1, R6.1, R8.1, R11.1, TP2.1 (1_1), U1.2 (Vout), U3.1 (AVDDVCSEL), U3.11 (AVDD)
+3V3: C13.2, C14.2, C18.1, C19.2, C22.1, C33.2, C34.2, C35.2, C36.2, C37.2, C38.2, C39.2, C43.2, R1.1, R5.1, R10.1, R12.1, R14.1, R25.1, R33.1, R34.1, TP10.1, U4.1 (IOVDD), U4.10 (IOVDD), U4.22 (IOVDD), U4.33 (IOVDD), U4.42 (IOVDD), U4.43 (ADC_AVDD), U4.44 (VREG_VIN), U4.48 (USB_VDD), U4.49 (IOVDD), U5.8 (VCC), U6.6 (VS), U8.8 (VCC), U9.2 (VO)
+5V: C1.2, C4.1, C7.1, C8.1, C42.2, D5.1 (K), F1.1, JP1.1 (A), L1.2, R4.1, R29.1, TP1.1 (1_1), U1.3 (Vin), U9.3 (VI)
+24V: C5.1, C6.1, D2.1 (A1), J1.1, R23.1, TP5.1 (1_1), U2.7 (VIN)
/+5V_HMI: C20.1, F1.2, J4.1, J4.6
/DE: U4.11 (GPIO8), U5.2 (~RE), U5.3 (DE)
/D_+: R13.2, U4.47 (USB_DP)
/D_-: R15.2, U4.46 (USB_DM)
/INA_SCL: R34.2, U4.35 (GPIO23), U6.5 (SCL)
/INA_SDA: R33.2, U4.38 (GPIO26/ADC0), U6.4 (SDA)
/I_ALERT: C23.1, R25.2, U4.39 (GPIO27/ADC1), U6.3 (~Alert)
/LS_SRC: Q7.1 (S), Q7.2 (S), Q7.3 (S), Q9.1 (S), Q9.2 (S), Q9.3 (S), R27.1
/MOTOR_24V: D3.1 (K), Q5.3 (S), R21.2, R23.4, U6.8 (Vbus)
/MOTOR_PWR: Q4.1 (G), R22.1, U4.31 (GPIO20)
/MOTOR_SW: C21.2, D4.1 (K), J5.2, JP6.1 (A), Q5.2 (D), TP13.1 (1_1)
/Mdir: J6.1, JP2.1 (A), R24.1, U4.27 (GPIO16)
/Mpwm: J6.2, JP3.1 (A), R26.1, U4.28 (GPIO17)
/OUT1: J7.1, Q6.1 (S), Q6.2 (S), Q6.3 (S), Q7.5 (D), U7.18 (SH1)
/OUT2: J7.2, Q8.1 (S), Q8.2 (S), Q8.3 (S), Q9.5 (D), U7.23 (SH2)
/RX: U4.12 (GPIO9), U5.1 (RO)
/S_N: R28.3, U7.20 (SN)
/S_P: R27.2, U7.21 (SP)
/TOF_INT: Q3.3 (D), R10.2, TP9.1 (1_1), U4.14 (GPIO11)
/TOF_SCL: Q1.3 (D), R1.2, TP3.1 (1_1), U4.16 (GPIO13)
/TOF_SDA: Q2.3 (D), R5.2, TP6.1 (1_1), U4.15 (GPIO12)
/TX: U4.6 (GPIO4), U5.4 (DI)
/VM: C24.1, C25.1, C26.1, C27.1, C28.1, C29.1, JP6.2 (B), Q6.5 (D), Q8.5 (D), U7.1 (VM)
/Vin+: R23.2, U6.10 (Vin+)
/Vin-: R23.3, U6.9 (Vin-)
/nFAULT: JP5.1 (A), U4.30 (GPIO19)
/nSLEEP: JP4.1 (A), U4.29 (GPIO18)
GND: BOOT1.1, C1.1, C2.1, C5.2, C6.2, C7.2, C8.2, C9.2, C10.2, C11.2, C12.2, C13.1, C14.1, C15.2, C16.2, C17.1, C18.2, C19.1, C20.2, C22.2, C23.2, C24.2, C25.2, C26.2, C27.2, C28.2, C31.2, C32.2, C33.1, C34.1, C35.1, C36.1, C37.1, C38.1, C39.1, C40.1, C41.1, C42.1, C43.1, D1.2 (A), D2.2 (A2), D4.2 (A), H1.1 (1_1), H2.1 (1_1), H3.1 (1_1), H4.1 (1_1), J1.2, J3.A1 (GND), J3.A12 (GND), J3.B1 (GND), J3.B12 (GND), J3.SH (SHIELD), J4.2, J4.5, J5.1, J6.3, LED1.2 (K), Q4.2 (S), R7.2, R17.2, R18.2, R19.2, R22.2, R24.2, R26.2, R28.4, R30.2, RST1.1, TP12.1 (1_1), U1.1 (GND), U2.6 (GND), U2.9 (GNDPAD), U3.2 (AVSSVCSEL), U3.3 (GND), U3.4 (GND2), U3.6 (GND3), U3.12 (GND4), U4.19 (TESTEN), U4.57 (GND), U5.5 (GND), U6.1 (A1), U6.2 (A0), U6.7 (GND), U7.5 (GND), U7.16 (GND), U7.25 (EP), U8.4 (GND), U9.1 (GND), Y1.2 (G), Y1.4 (G)
unnamed: BOOT1.2, R31.1
unnamed: C12.1, R9.2
unnamed: C16.1, R32.1, Y1.3
unnamed: C3.1, D1.1 (K), L1.1, U2.8 (PH)
unnamed: C21.1, D3.2 (A), Q5.1 (G), R20.1, R21.1
unnamed: D5.2 (A), J3.A4 (VBUS), J3.A9 (VBUS), J3.B4 (VBUS), J3.B9 (VBUS)
unnamed: J3.A5 (CC1), R19.1
unnamed: J3.B5 (CC2), R18.1
unnamed: J3.A6 (D+), J3.B6 (D+), R13.1
unnamed: J3.A7 (D-), J3.B7 (D-), R15.1
unnamed: JP1.2 (B), R3.1
unnamed: JP2.2 (B), U7.15 (PH)
unnamed: JP3.2 (B), U7.14 (EN)
unnamed: JP4.2 (B), U7.13 (nSLEEP)
unnamed: JP5.2 (B), U7.9 (nFAULT)
unnamed: LED1.1 (A), R3.2
unnamed: Q1.2 (S), R2.2, TP15.1, U3.10 (SCL)
unnamed: Q2.2 (S), R6.2, TP16.1, U3.9 (SDA)
unnamed: Q3.2 (S), R11.2, TP17.1, U3.7 (GPIO1)
unnamed: Q4.3 (D), R20.2
unnamed: Q6.4 (G), U7.17 (GH1)
unnamed: Q7.4 (G), U7.19 (GL1)
unnamed: Q8.4 (G), U7.24 (GH2)
unnamed: Q9.4 (G), U7.22 (GL2)
unnamed: R27.4, R28.1
unnamed: C3.2, U2.1 (BOOT)
unnamed: C4.2, C11.1, R4.2, R7.1, R9.1, U2.4 (VSENSE)
unnamed: R8.2, TP8.1, U3.5 (XSHUT)
unnamed: U4.52 (QSPI_SCLK), U8.6 (CLK)
unnamed: U4.53 (QSPI_SD0), U8.5 (DI/IO_{0})
unnamed: U4.55 (QSPI_SD1), U8.2 (DO/IO_{1})
unnamed: U4.54 (QSPI_SD2), U8.3 (~WP/IO_{2})
unnamed: U4.51 (QSPI_SD3), U8.7 (~HOLD/~RESET/IO_{3})
unnamed: R12.2, RST1.2, TP11.1 (1_1), U4.26 (RUN)
unnamed: TP4.1, U4.24 (SWCLK)
unnamed: TP7.1, U4.25 (SWDIO)
unnamed: C15.1, U4.20 (XIN), Y1.1
unnamed: R32.2, U4.21 (XOUT)
unnamed: R31.2, U4.56 (~QSPI_SS), U8.1 (~CS)
unnamed: J4.3, R14.2, R16.1, U5.6 (A)
unnamed: J4.4, R16.2, R17.1, U5.7 (B)
unnamed: C31.1, U7.7 (AVDD)
unnamed: C30.1, U7.3 (CPH)
unnamed: C30.2, U7.4 (CPL)
unnamed: C32.1, U7.8 (DVDD)
unnamed: TP14.1 (1_1), U7.11 (SO)
unnamed: C29.2, U7.2 (VCP)
unnamed: R29.2, R30.1, U7.6 (VREF)

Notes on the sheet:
J4 pin-out (6P6C, straight or reversed cord): 1 = +5V 2 = GND 3 = A 4 = B 5 = GND 6 = +5V A reversed cord only swaps A and B: the HMI board detects it. Never plug J4 into a telephone wall socket.
24 V supply input, 15 A pluggable terminal (it carries the motor current)
Link to the HMI board: RS-485 over an RJ11 cord
J6: DIR, PWM, logic GND to an external driver (MD10C), used when the bridge is bypassed.
addr: 0x52
Mounting holes
Motor supply: shunt + INA226, switch, driver connectors
Motor driver: DRV8701E + 4 x BSC028N06NS H-bridge (15 A, 25 kHz PWM)
AVDD 2.8 V (2.6 - 3.5 V)
D2 clamps motor and hot-plug spikes below the 40 V absolute maximum of U2 and U6. C6: 24 V bulk.
MOTOR_PWR high: Q5 on (Vgs -12 V). R22 keeps it off in reset. C21 / R20: ~15 ms soft start. Cut only with the PWM at 0.
INA226: I2C address 0x40 (A0 = A1 = GND), VS = 3.3 V, alert on GPIO27. Own I2C bus (RP2040 I2C1): INA_SDA GPIO26, INA_SCL GPIO23, R33 / R34 3.3k pull-ups. R23 2 mOhm: +-41 A full scale, 1.25 mA resolution, 0.34 W at 13 A. Kelvin-connect Vin+ / Vin- right at the R23 pads. +24V / MOTOR_24V / MOTOR_SW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
Ceramic output compensation (TI SLVA237): L1 22 uH, C7 + C8 2 x 47 uF: f_LC ~ 4.7 kHz. C4 / R9 / C12 / C11: crossover 14-27 kHz, phase margin > 60 deg, 0.1 to 1.5 A.
R14 / R17: bias. R16 (DNP): 120R termination, only for cords over ~5 m (then R14 / R17 = 680R).
ENA left open: internal 1.5 MOhm pull-up
PH = DIR, EN = PWM. EN low = brake (both low sides on). nSLEEP low = FETs held off; its internal 115k pull-down keeps the bridge off during a reset or the bootloader. Firmware: nSLEEP high once MOTOR_SW is up, PWM 1 ms later; nFAULT: MCU pull-up on. Current limit, cycle by cycle: R27 + R28 = 4 mOhm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
24 V input, 5 V supply (TPS5430 buck), power LED
Optical height monitor
Wire colours (net classes, see the project settings)
MCU: RP2040, QSPI flash, USB
Decoupling, one per pin, next to it on the PCB: C13 C14 C33-C36 IOVDD x6, C37 USB_VDD, C38 ADC_AVDD, C19 VREG_VIN, C39 flash, C17 C40 DVDD x2, C41 VREG_VOUT. BOOT1 held at reset: USB drive (UF2). SWD: TP4, TP7, TP12. D5: USB-C feeds +5V (logic and HMI, not the motor) without 24 V. With 24 V the TPS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
Q1 / Q2 / Q3 (BSS138, Vgs(th) <= 1.5 V): level shifters, NXP AN10441. 3.3 V side: TOF_SCL, TOF_SDA, TOF_INT (RP2040 GPIO13, 12, 11; I2C0), pulled up by R1 / R5 / R10 to +3V3. Sensor side (2.8 V): SCL, SDA and GPIO1 of U3, R2 / R6 / R11 to +2V8. A low from the RP2040 reaches the sensor at about 0.2 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
24 V and motor power, 15 A path (thick): +24V, MOTOR_24V, MOTOR_SW, VM, OUT1 / OUT2, LS_SRC
+5V, +5V_HMI (USB-C VBUS through D5 on the bench)
+3V3 (U9: RP2040, flash, RS-485, INA226)
+2V8 (height sensor, its side of Q1 / Q2 / Q3)
+1V1 (RP2040 core)
GND
Motor command: Mdir, Mpwm, nSLEEP, nFAULT, MOTOR_PWR, I_ALERT
H-bridge gates (GH1 / GL1 / GH2 / GL2)
Current sense, Kelvin: INA226 Vin+ / Vin-, DRV8701 SP / SN
Buses: I2C (3.3 V and 2.8 V sides), ToF interrupt, RS-485, USB, QSPI flash
Other signals (KiCad default)
Assembly (README): JLCPCB Economic PCBA, top side, 0402 minimum (no 0201). Hand-soldered, out of the BOM and position files: L1, F1, U1, R23 / R27 / R28, C6, Q5, Q6-Q9, J3. JLCPCB solders the through-hole parts by hand (no loading fee).

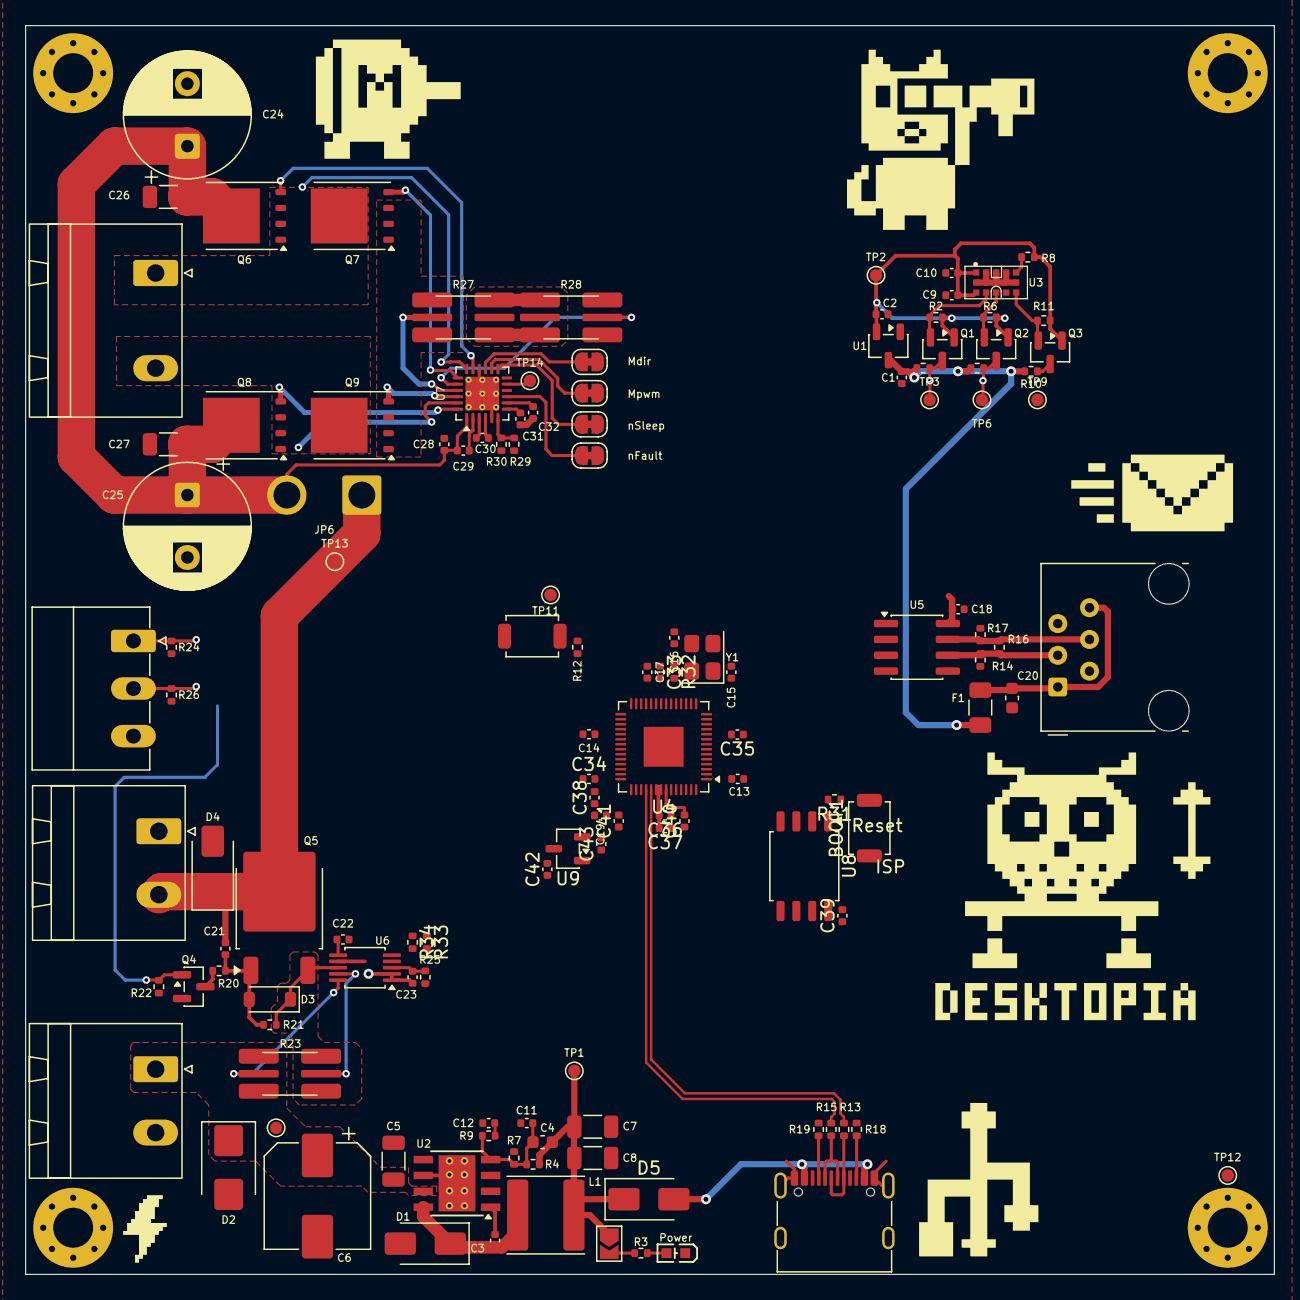
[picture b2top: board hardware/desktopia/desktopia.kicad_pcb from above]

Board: 2 copper layers, 100.0 x 100.0 mm, 132 parts (0 on the bottom side), 79 nets.
